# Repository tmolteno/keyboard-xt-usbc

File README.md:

## Interface an IBM PC-XT original keyboard to USB-C

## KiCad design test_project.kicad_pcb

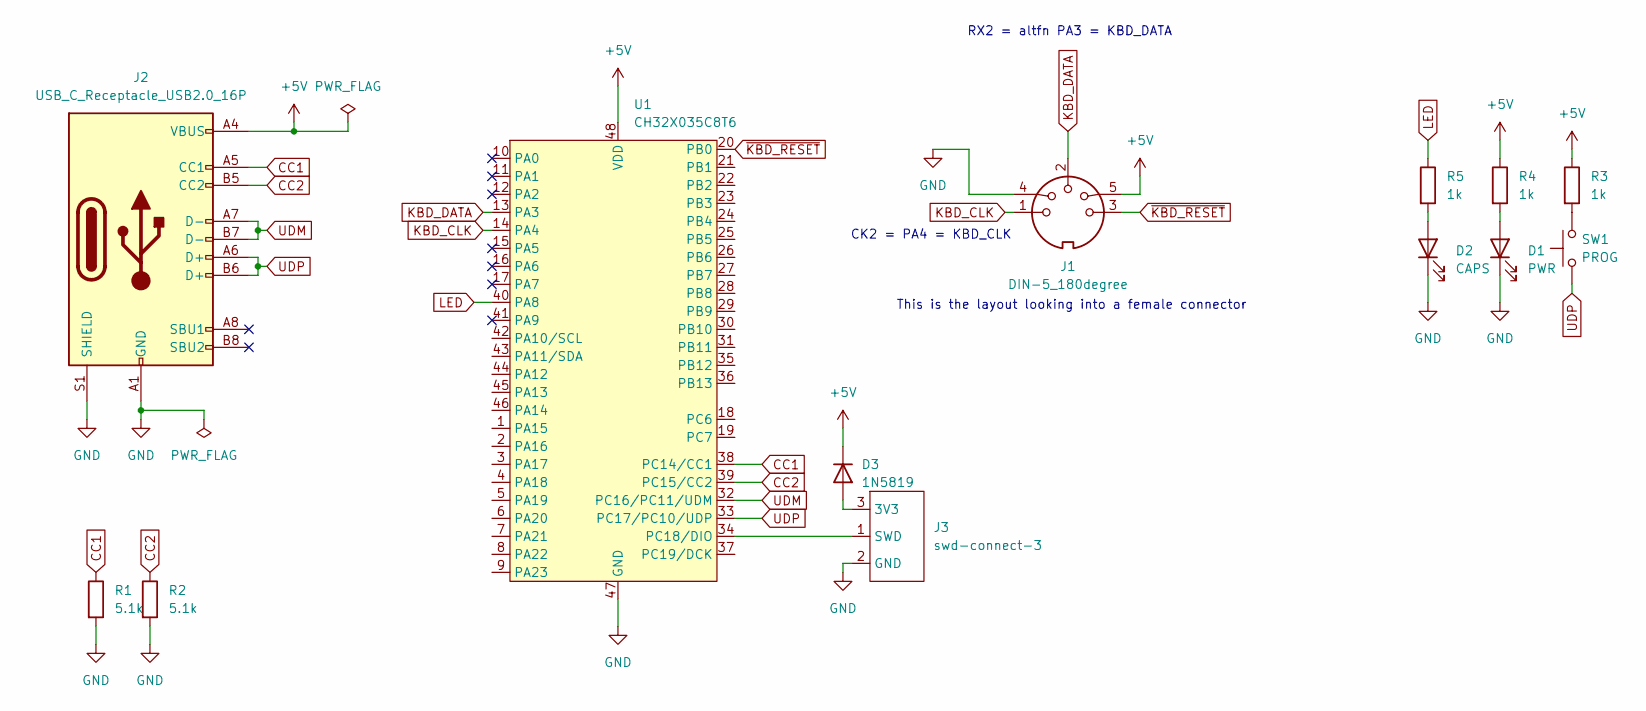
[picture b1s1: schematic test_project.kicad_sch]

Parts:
D1: PWR; LED_0603_1608Metric; LCSC C2286
D2: CAPS; LED_0603_1608Metric; LCSC C2290
D3: 1N5819; D_SOD-323; LCSC C191023
J1: DIN-5_180degree; HOOYA-DIN_504B_M5; LCSC C20611696
J2: USB_C_Receptacle_USB2.0_16P; USB_C_Receptacle_G-Switch_GT-USB-7010ASV; LCSC C2765186
J3: swd-connect-3; swd-connect-3-mcu-tight
R1, R2: 5.1k; R_0402_1005Metric; LCSC C25905
R3, R4, R5: 1k; R_0402_1005Metric; LCSC C11702
SW1: PROG; SW_Push_1P1T_XKB_TS-1187A; LCSC C318884
U1: CH32X035C8T6; LQFP-48_7x7mm_P0.5mm; LCSC C29779902

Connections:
+5V: D3.1 (K), J1.5, J2.A4 (VBUS), J2.A9 (VBUS), J2.B4 (VBUS), J2.B9 (VBUS), R3.1, R4.1, U1.48 (VDD)
CC1: J2.A5 (CC1), R1.1, U1.38 (PC14/CC1)
CC2: J2.B5 (CC2), R2.1, U1.39 (PC15/CC2)
GND: D1.1 (K), D2.1 (K), J1.4, J2.A1 (GND), J2.A12 (GND), J2.B1 (GND), J2.B12 (GND), J2.S1 (SHIELD), J3.2 (GND), R1.2, R2.2, U1.47 (GND)
KBD_CLK: J1.1, U1.14 (PA4)
KBD_DATA: J1.2, U1.13 (PA3)
LED: R5.1, U1.40 (PA8)
unnamed: D1.2 (A), R4.2
unnamed: D2.2 (A), R5.2
unnamed: D3.2 (A), J3.3 (3V3)
unnamed: J3.1 (SWD), U1.34 (PC18/DIO)
unnamed: R3.2, SW1.2
UDM: J2.A7 (D-), J2.B7 (D-), U1.32 (PC16/PC11/UDM)
UDP: J2.A6 (D+), J2.B6 (D+), SW1.1, U1.33 (PC17/PC10/UDP)
~KBD_RESET: J1.3, U1.20 (PB0)

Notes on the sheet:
RX2 = altfn PA3 = KBD_DATA
CK2 = PA4 = KBD_CLK
This is the layout looking into a female connector

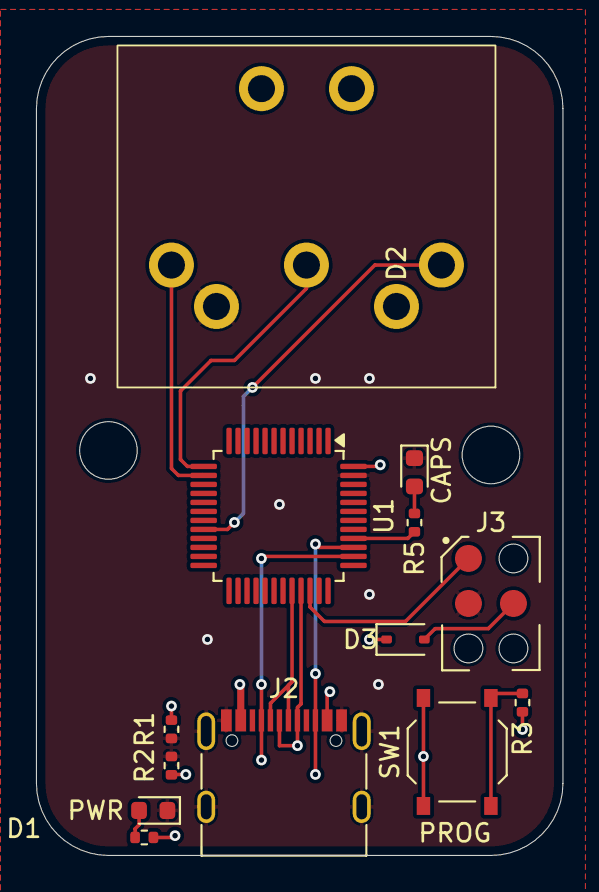
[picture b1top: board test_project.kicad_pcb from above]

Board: 4 copper layers, 29.2 x 45.5 mm, 13 parts (0 on the bottom side), 15 nets.

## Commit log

2025-08-13 Added some firmware which seems to work.
2025-08-15 Initial plan
2025-08-15 Refactor XT keyboard interface into modular functions
